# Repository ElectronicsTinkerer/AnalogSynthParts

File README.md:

# AnalogSynthParts
A collection of analog/midi related synth boards and schematics

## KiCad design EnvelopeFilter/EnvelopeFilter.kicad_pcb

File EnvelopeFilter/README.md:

# Envelope Filter
A simple ADSR-controlled VCF for use in panel-mount synthesizers.

## Interface
There are two inputs to the board:
- `IN` - Signal input (±15Vpp max) to be put into the envelope.
- `GATE` - Gate (active high) input for the ADSR envelope. Rising edge is treated as trigger.

 and one output:
 - `OUT` - Signal out of board after envelope has been applied.   

There is a bunch of 3-pin headers for connection to external potentiometers and switches to enable/disable various features like filter bypasses, manual frequency cutoff, and resonance.

### Power
This board is designed to be run off ±15V but with a few resistor swaps, it could be run off ±12V.   

## Schematic
The schematic for the ADSR section of the board is based off the *Soundtronics ADSR Type 1* design. It uses an `AS3310` ADSR control IC to generate the envelope control voltage. This is then fed through a resistor divider into the frequency control on an AS3320 VCF to adjust the cutoff frequency of each section of the filter, which is then sent to the output.  

## Board
The board is designed in a similar manner to the other ones in this repository, where it is supported by the potentiometers' leads. The pots are placed 1 inch apart for easy hole placement when designing the panel.

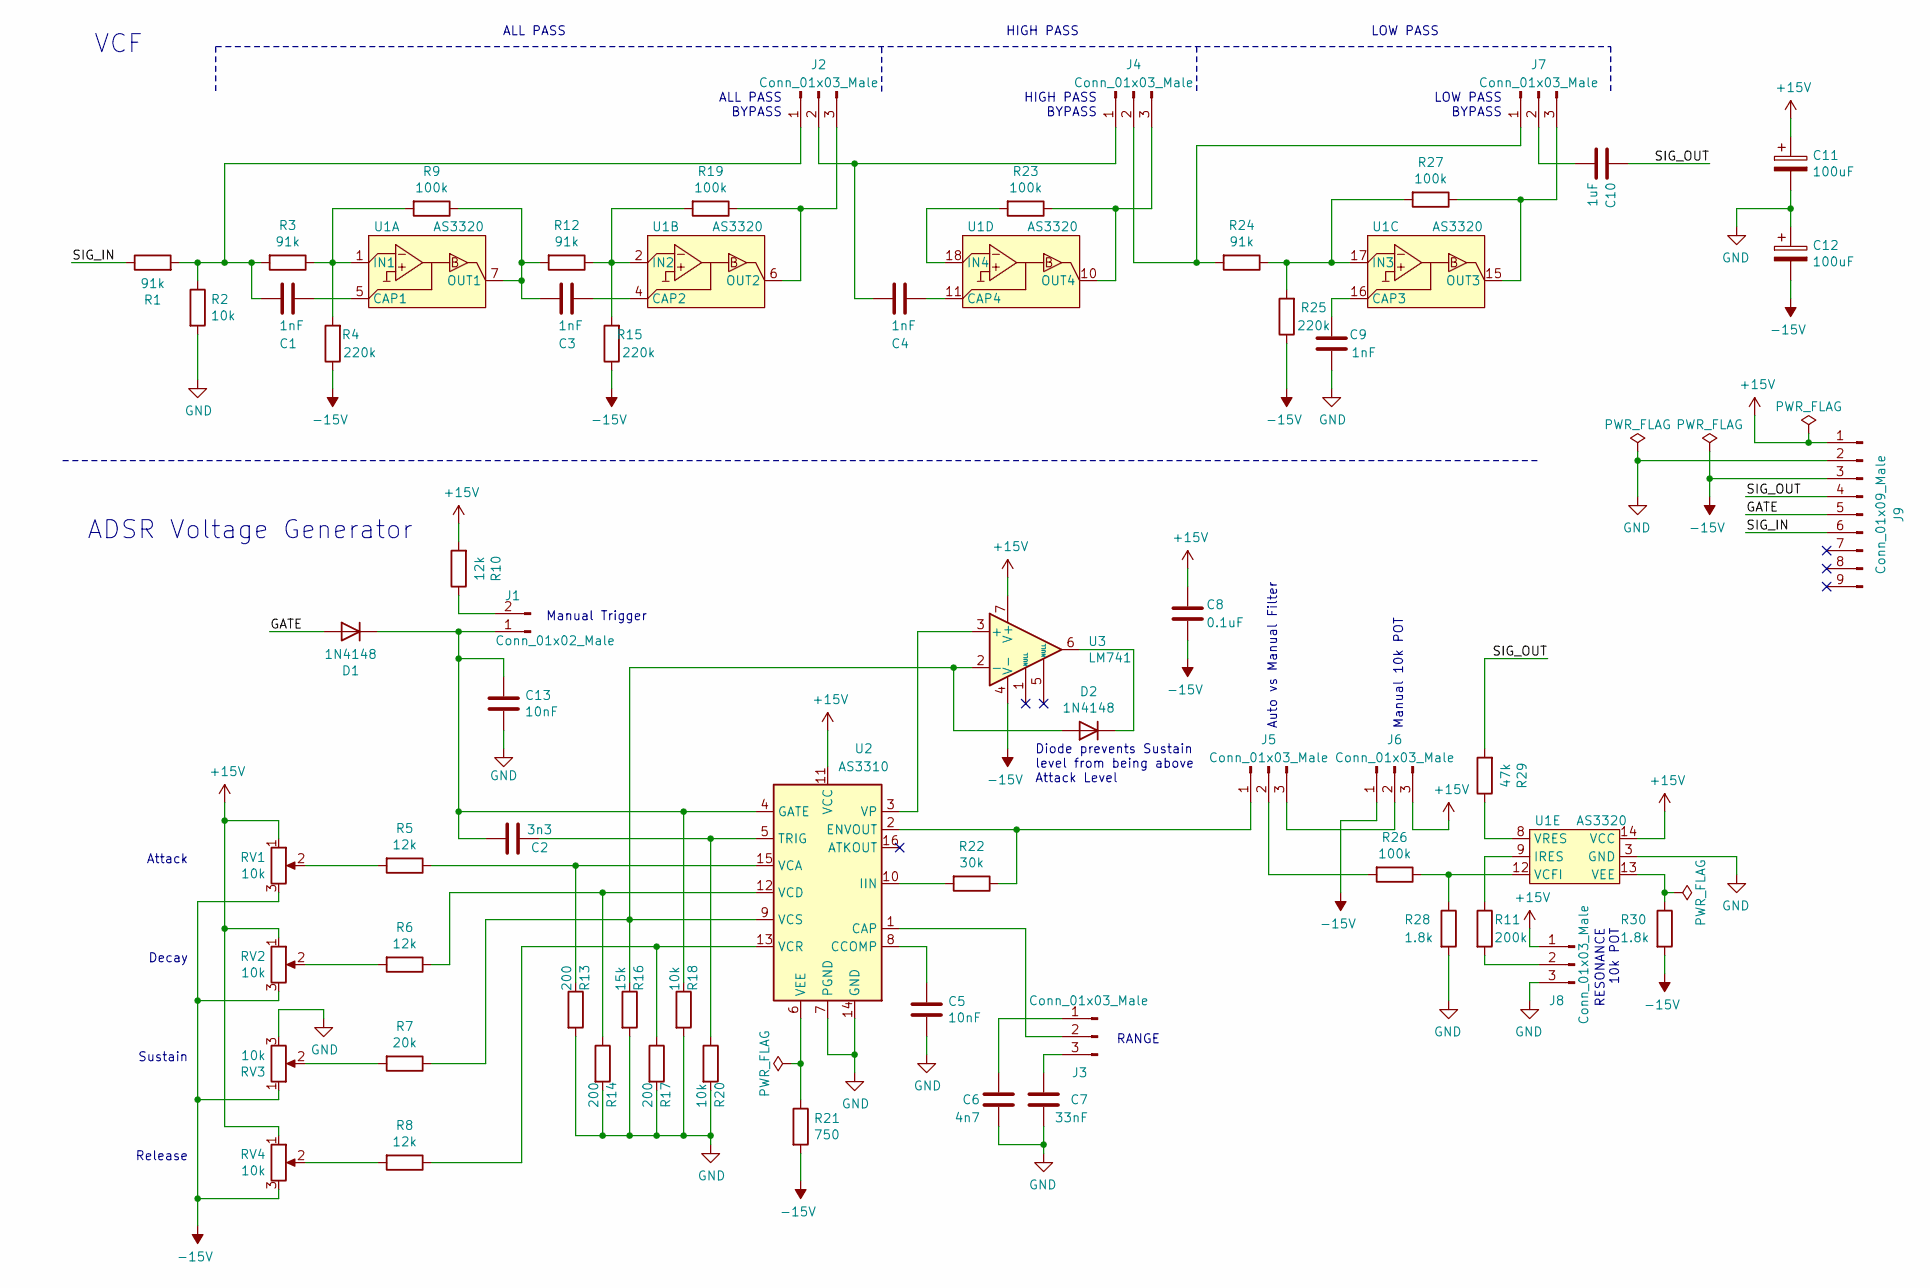
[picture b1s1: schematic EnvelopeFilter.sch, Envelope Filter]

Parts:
C1, C3, C4, C9: 1nF; C_Disc_D4.3mm_W1.9mm_P5.00mm
C2: 3n3; C_Disc_D4.3mm_W1.9mm_P5.00mm
C5: 10nF; C_Disc_D4.3mm_W1.9mm_P5.00mm
C6: 4n7; C_Disc_D4.3mm_W1.9mm_P5.00mm
C7: 33nF; C_Disc_D4.3mm_W1.9mm_P5.00mm
C8: 0.1uF; C_Disc_D4.3mm_W1.9mm_P5.00mm
C10: 1uF; C_Disc_D4.3mm_W1.9mm_P5.00mm
C11, C12: 100uF; CP_Radial_D8.0mm_P3.50mm
C13: 10nF; R_Axial_DIN0204_L3.6mm_D1.6mm_P5.08mm_Horizontal
D1, D2: 1N4148; D_DO-35_SOD27_P7.62mm_Horizontal
J1: Conn_01x02_Male; PinHeader_1x02_P2.54mm_Vertical
J2, J3, J4, J5, J6, J7, J8: Conn_01x03_Male; PinHeader_1x03_P2.54mm_Vertical
J9: Conn_01x09_Male; PinHeader_1x09_P2.54mm_Vertical
R1, R3, R12, R24: 91k; R_Axial_DIN0204_L3.6mm_D1.6mm_P5.08mm_Horizontal
R2, R18, R20: 10k; R_Axial_DIN0204_L3.6mm_D1.6mm_P5.08mm_Horizontal
R4, R15, R25: 220k; R_Axial_DIN0204_L3.6mm_D1.6mm_P5.08mm_Horizontal
R5, R6, R8, R10: 12k; R_Axial_DIN0204_L3.6mm_D1.6mm_P5.08mm_Horizontal
R7: 20k; R_Axial_DIN0204_L3.6mm_D1.6mm_P5.08mm_Horizontal
R9, R19, R23, R26, R27: 100k; R_Axial_DIN0204_L3.6mm_D1.6mm_P5.08mm_Horizontal
R11: 200k; R_Axial_DIN0204_L3.6mm_D1.6mm_P5.08mm_Horizontal
R13, R14, R17: 200; R_Axial_DIN0204_L3.6mm_D1.6mm_P5.08mm_Horizontal
R16: 15k; R_Axial_DIN0204_L3.6mm_D1.6mm_P5.08mm_Horizontal
R21: 750; R_Axial_DIN0414_L11.9mm_D4.5mm_P5.08mm_Vertical
R22: 30k; R_Axial_DIN0204_L3.6mm_D1.6mm_P5.08mm_Horizontal
R28, R30: 1.8k; R_Axial_DIN0204_L3.6mm_D1.6mm_P5.08mm_Horizontal
R29: 47k; R_Axial_DIN0204_L3.6mm_D1.6mm_P5.08mm_Horizontal
RV1, RV2, RV3, RV4: 10k; Potentiometer_Piher_PC-16_Single_Horizontal
U1: AS3320; DIP-18_W7.62mm
U2: AS3310; DIP-16_W7.62mm_Socket_LongPads
U3: LM741; DIP-8_W7.62mm_Socket_LongPads

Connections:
+15V: C8.2, C11.1, J6.3, J8.1, J9.1, R10.2, RV1.1, RV2.1, RV4.1, U1.14 (VCC), U2.11 (VCC), U3.7 (V+)
-15V: C8.1, C12.2, J6.1, J9.3, R4.1, R15.1, R21.2, R25.1, R30.2, RV1.3, RV2.3, RV3.1, RV4.3, U3.4 (V-)
/GATE: D1.2 (A), J9.5
/SIG_IN: J9.6, R1.1
/SIG_OUT: C10.2, J9.4, R29.2
GND: C5.1, C6.1, C7.1, C9.1, C11.2, C12.1, C13.1, J8.3, J9.2, R2.2, R13.2, R14.2, R16.2, R17.2, R18.2, R20.2, R28.2, RV3.3, U1.3 (GND), U2.7 (PGND), U2.14 (GND)
unnamed: C1.1, J2.1, R1.2, R2.1, R3.2
unnamed: C1.2, U1.5 (CAP1)
unnamed: C2.1, R20.1, U2.5 (TRIG)
unnamed: C3.1, R9.1, R12.2, U1.7 (OUT1)
unnamed: C3.2, U1.4 (CAP2)
unnamed: C4.1, J2.2, J4.1
unnamed: C4.2, U1.11 (CAP4)
unnamed: C5.2, U2.8 (CCOMP)
unnamed: C6.2, J3.1
unnamed: C7.2, J3.3
unnamed: C9.2, U1.16 (CAP3)
unnamed: C10.1, J7.2
unnamed: C2.2, C13.2, D1.1 (K), J1.1, R18.1, U2.4 (GATE)
unnamed: D2.1 (K), U3.6
unnamed: D2.2 (A), R7.1, R16.1, U2.9 (VCS), U3.2 (-)
unnamed: J1.2, R10.1
unnamed: J2.3, R19.1, U1.6 (OUT2)
unnamed: J3.2, U2.1 (CAP)
unnamed: J4.2, J7.1, R24.2
unnamed: J4.3, R23.1, U1.10 (OUT4)
unnamed: J5.1, R22.1, U2.2 (ENVOUT)
unnamed: J5.2, R26.2
unnamed: J5.3, J6.2
unnamed: J7.3, R27.1, U1.15 (OUT3)
unnamed: J8.2, R11.2
unnamed: R3.1, R4.2, R9.2, U1.1 (IN1)
unnamed: R5.2, RV1.2
unnamed: R6.2, RV2.2
unnamed: R7.2, RV3.2
unnamed: R8.2, RV4.2
unnamed: R11.1, U1.9 (IRES)
unnamed: R12.1, R15.2, R19.2, U1.2 (IN2)
unnamed: R5.1, R13.1, U2.15 (VCA)
unnamed: R6.1, R14.1, U2.12 (VCD)
unnamed: R8.1, R17.1, U2.13 (VCR)
unnamed: R21.1, U2.6 (VEE)
unnamed: R22.2, U2.10 (IIN)
unnamed: R23.2, U1.18 (IN4)
unnamed: R24.1, R25.2, R27.2, U1.17 (IN3)
unnamed: R26.1, R28.1, U1.12 (VCFI)
unnamed: R29.1, U1.8 (VRES)
unnamed: R30.1, U1.13 (VEE)
unnamed: U2.3 (VP), U3.3 (+)

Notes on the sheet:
RANGE
Diode prevents Sustain level from being above Attack Level
ADSR Voltage Generator
VCF
Manual Trigger
Attack
Decay
Sustain
Release
ALL PASS
HIGH PASS
LOW PASS
ALL PASS BYPASS
HIGH PASS BYPASS
LOW PASS BYPASS
Auto vs Manual Filter
Manual 10k POT
RESONANCE 10k POT

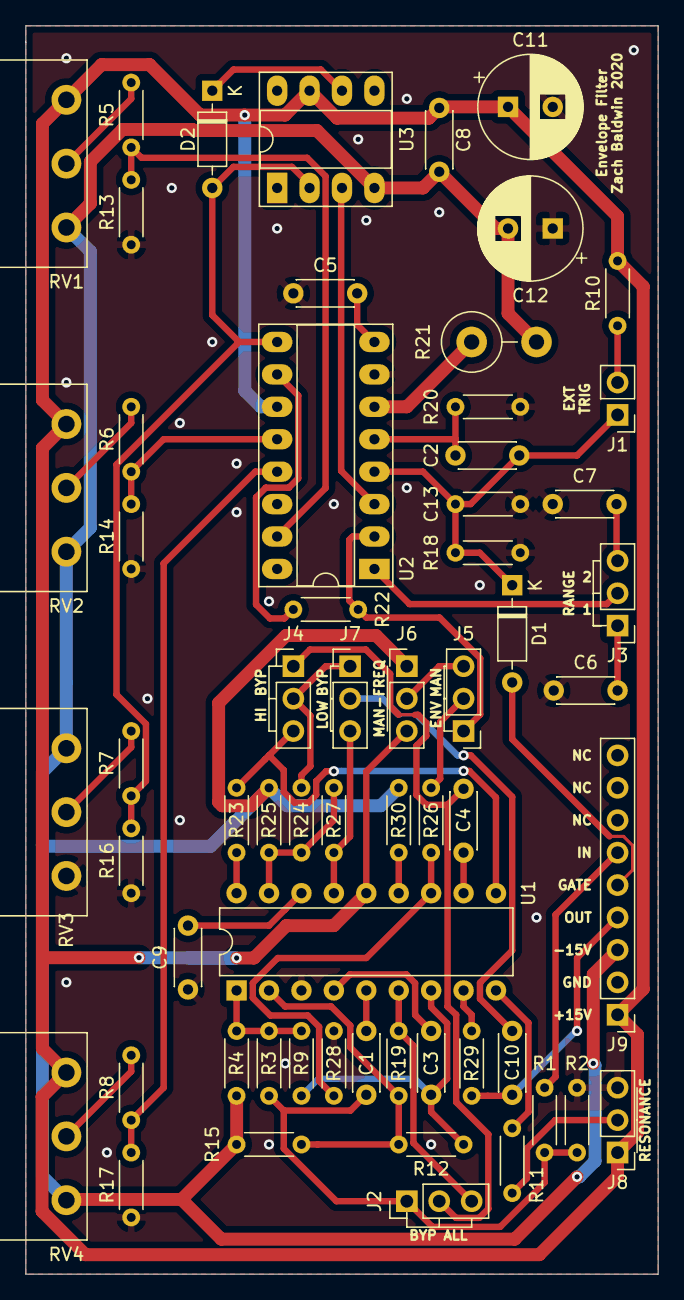
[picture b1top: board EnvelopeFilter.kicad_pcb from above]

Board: 2 copper layers, 49.5 x 97.8 mm, 61 parts (0 on the bottom side), 49 nets.

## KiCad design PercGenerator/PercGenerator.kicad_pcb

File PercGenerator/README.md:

# Percussion Synthesizer
A single op-amp "percussion synthesizer" redrawn from Forrest Mims III's *Getting Started in Electronics*

## Picture

## Interface
There are four potentiometers on the board. The leftmost three are for resonance cutoff (CCW is for cutoff, CW for resonance) and the rightmost potentiometer is gain out.   
This board uses the same connector pin out as the 555 Synth Module and each of the pins is marked on the board. Since not all of the pins were needed, four of them are marked "NC" and are unconnected. The remaining signals are:
- `T` - Triggers sound on both rising and falling edge
- `OUT` - Output waveform, this is connected via a potentiometer and a capacitor internally.

### Power
I run this board off ±15V, however, Mims uses ±9V in his book, so anywhere in that range should be fine. (While testing this circuit before I created the PCBs, I just used a +10v supply fed into a L7805 to create ±5V and that worked just fine).

## Schematic
The schematic is a simple feedback oscillator with three 1M potentiometers to adjust the resonance. The schematic is the same as one in Mims' book, except for the addition of a transistor in parallel with the trigger switch.

## Board
The board really could have been laid out however one wanted, but I chose to put the control potentiometers 1" apart on one side of the board. There are two "mounting holes" that are grounded in case anyone wants to mount the board more securely than just being held on via the potentiometers.

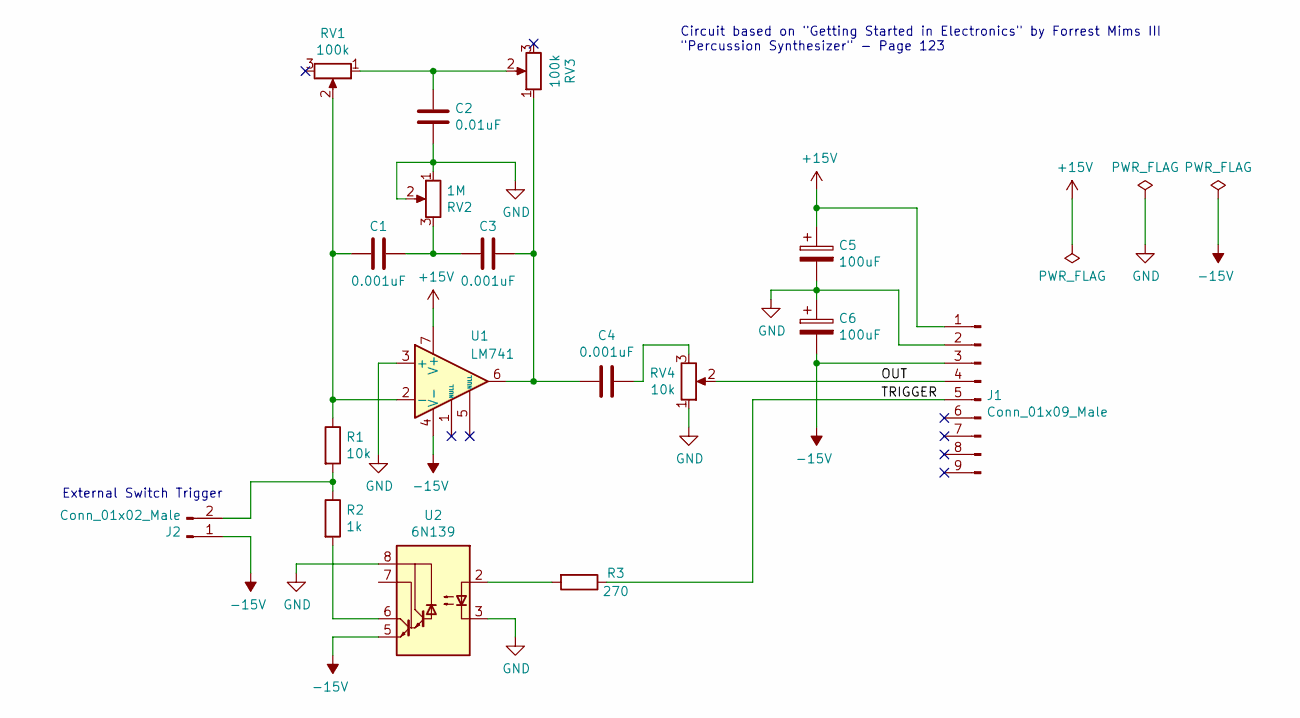
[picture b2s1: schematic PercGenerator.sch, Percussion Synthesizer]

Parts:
C1, C3, C4: 0.001uF; C_Disc_D4.3mm_W1.9mm_P5.00mm
C2: 0.01uF; C_Disc_D4.3mm_W1.9mm_P5.00mm
C5, C6: 100uF; CP_Radial_D8.0mm_P3.50mm
J1: Conn_01x09_Male; PinHeader_1x09_P2.54mm_Vertical
J2: Conn_01x02_Male; PinHeader_1x02_P2.54mm_Vertical
R1: 10k; R_Axial_DIN0204_L3.6mm_D1.6mm_P5.08mm_Horizontal
R2: 1k; R_Axial_DIN0204_L3.6mm_D1.6mm_P5.08mm_Horizontal
R3: 270; R_Axial_DIN0204_L3.6mm_D1.6mm_P5.08mm_Horizontal
RV1, RV3: 100k; Potentiometer_Piher_PC-16_Single_Horizontal
RV2: 1M; Potentiometer_Piher_PC-16_Single_Horizontal
RV4: 10k; Potentiometer_Piher_PC-16_Single_Horizontal
U1: LM741; DIP-8_W7.62mm_LongPads
U2: 6N139; DIP-8_W7.62mm_LongPads

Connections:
+15V: C5.1, J1.1, U1.7 (V+)
-15V: C6.2, J1.3, J2.1, U1.4 (V-), U2.5 (GND)
/OUT: J1.4, RV4.2
/TRIGGER: J1.5, R3.1
GND: C2.2, C5.2, C6.1, J1.2, RV2.1, RV2.2, RV4.1, U1.3 (+), U2.3 (C2), U2.8 (VCC)
unnamed: C1.1, C3.2, RV2.3
unnamed: C1.2, R1.1, RV1.2, U1.2 (-)
unnamed: C2.1, RV1.1, RV3.2
unnamed: C3.1, C4.2, RV3.1, U1.6
unnamed: C4.1, RV4.3
unnamed: J2.2, R1.2, R2.1
unnamed: R2.2, U2.6 (VO2)
unnamed: R3.2, U2.2 (C1)

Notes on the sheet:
Circuit based on "Getting Started in Electronics" by Forrest Mims III "Percussion Synthesizer" - Page 123
External Switch Trigger

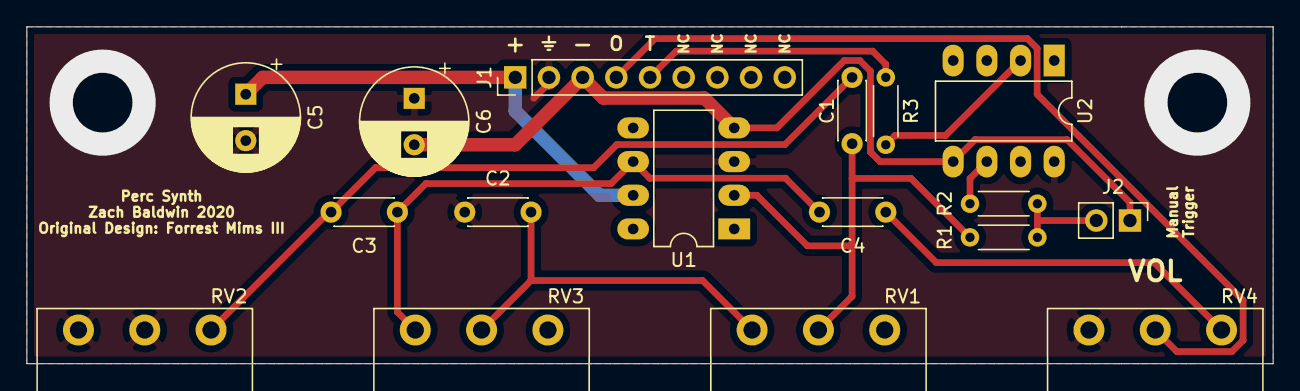
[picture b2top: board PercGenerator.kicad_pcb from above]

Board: 2 copper layers, 94.0 x 25.4 mm, 17 parts (0 on the bottom side), 13 nets.

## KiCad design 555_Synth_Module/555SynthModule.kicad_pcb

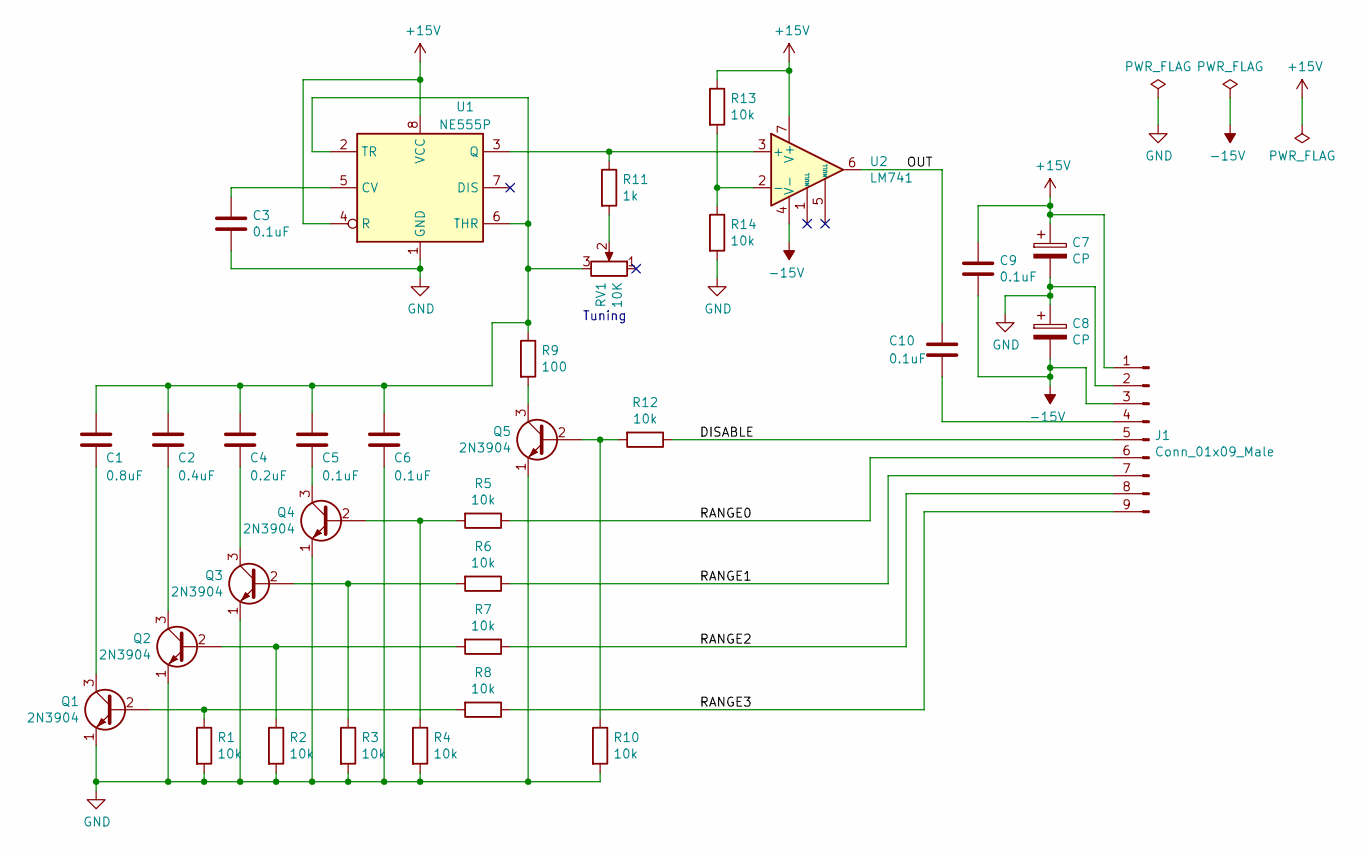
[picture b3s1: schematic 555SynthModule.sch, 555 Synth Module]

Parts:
C1: 0.8uF; C_Disc_D4.3mm_W1.9mm_P5.00mm
C2: 0.4uF; C_Disc_D4.3mm_W1.9mm_P5.00mm
C3, C5, C6, C9, C10: 0.1uF; C_Disc_D4.3mm_W1.9mm_P5.00mm
C4: 0.2uF; C_Disc_D4.3mm_W1.9mm_P5.00mm
C7, C8: CP; CP_Radial_D8.0mm_P3.50mm
J1: Conn_01x09_Male; PinHeader_1x09_P2.54mm_Vertical
Q1, Q2, Q3, Q4, Q5: 2N3904; TO-92_Inline
R1, R2, R3, R4, R5, R6, R7, R8, R10, R12, R13, R14: 10k; R_Axial_DIN0204_L3.6mm_D1.6mm_P5.08mm_Horizontal
R9: 100; R_Axial_DIN0204_L3.6mm_D1.6mm_P5.08mm_Horizontal
R11: 1k; R_Axial_DIN0204_L3.6mm_D1.6mm_P5.08mm_Horizontal
RV1: 10K; Potentiometer_Piher_PC-16_Single_Horizontal
U1: NE555P; DIP-8_W7.62mm
U2: LM741; DIP-8_W7.62mm

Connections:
+15V: C7.1, C9.1, J1.1, R13.1, U1.4 (R), U1.8 (VCC), U2.7 (V+)
-15V: C8.2, C9.2, J1.3, U2.4 (V-)
/DISABLE: J1.5, R12.1
/OUT: C10.1, U2.6
/RANGE0: J1.6, R5.1
/RANGE1: J1.7, R6.1
/RANGE2: J1.8, R7.1
/RANGE3: J1.9, R8.1
GND: C3.2, C6.2, C7.2, C8.1, J1.2, Q1.1 (E), Q2.1 (E), Q3.1 (E), Q4.1 (E), Q5.1 (E), R1.2, R2.2, R3.2, R4.2, R10.2, R14.2, U1.1 (GND)
unnamed: C1.1, C2.1, C4.1, C5.1, C6.1, R9.1, RV1.3, U1.2 (TR), U1.6 (THR)
unnamed: C1.2, Q1.3 (C)
unnamed: C2.2, Q2.3 (C)
unnamed: C3.1, U1.5 (CV)
unnamed: C4.2, Q3.3 (C)
unnamed: C5.2, Q4.3 (C)
unnamed: C10.2, J1.4
unnamed: Q1.2 (B), R1.1, R8.2
unnamed: Q2.2 (B), R2.1, R7.2
unnamed: Q3.2 (B), R3.1, R6.2
unnamed: Q4.2 (B), R4.1, R5.2
unnamed: Q5.2 (B), R10.1, R12.2
unnamed: Q5.3 (C), R9.2
unnamed: R11.1, U1.3 (Q), U2.3 (+)
unnamed: R11.2, RV1.2
unnamed: R13.2, R14.1, U2.2 (-)

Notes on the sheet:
Tuning

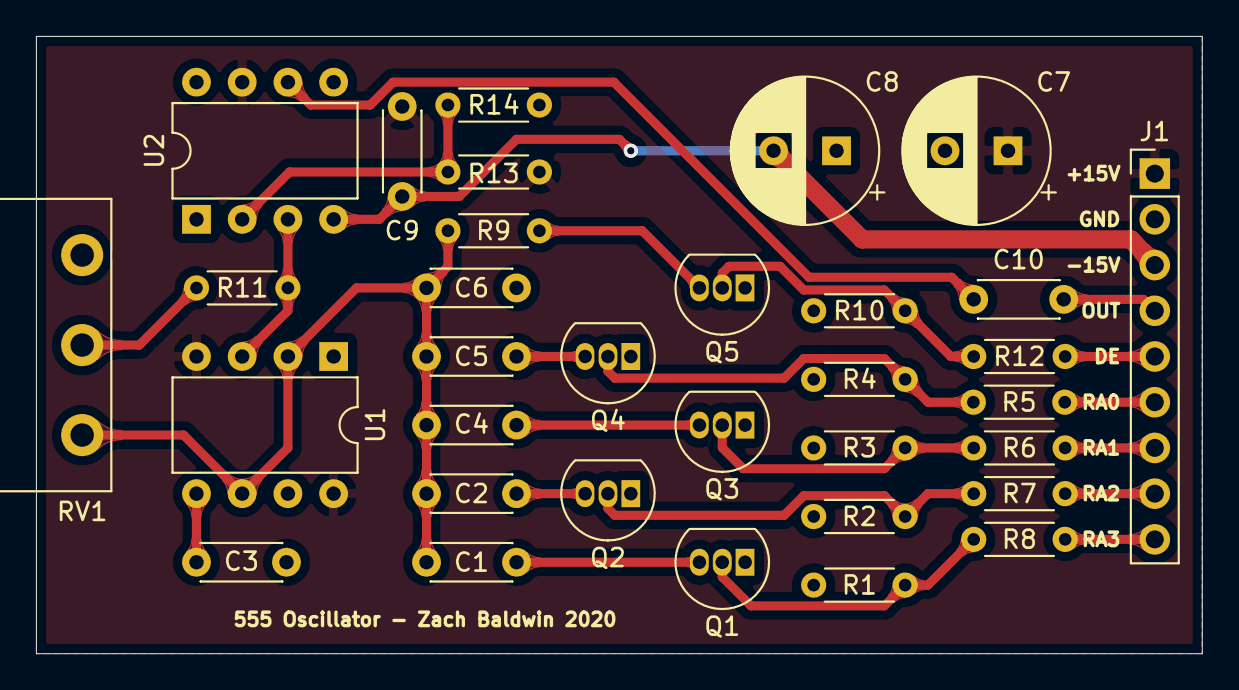
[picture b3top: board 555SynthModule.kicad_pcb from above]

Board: 2 copper layers, 64.8 x 34.3 mm, 33 parts (0 on the bottom side), 25 nets.

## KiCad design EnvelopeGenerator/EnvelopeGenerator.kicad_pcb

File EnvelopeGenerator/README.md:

# Envelope Generator
A simple ADSR-controlled VCA for use in panel-mount synthesizers.

## Interface
There are two inputs to the board:
- `IN` - Signal input (±15Vpp max) to be put into the envelope.
- `GATE` - Gate (active high) input for the ADSR envelope. Rising edge is treated as trigger.

 and one output:
 - `OUT` - Signal out of board after envelope has been applied.

### Power
Unlike the other modules in this repository, this board needs a ±15V supply since one of the ICs has its own set of ±12V regulators. (Although, I suppose you could just bypass the regulators if you wanted to run it off ±12V).   

## Schematic
The schematic for the ADSR section of the board is based off the *Soundtronics ADSR Type 1* design. It uses an `AS3310` ADSR control IC to generate the envelope control voltage. This is then fed through a resistor divider into the gain control on an AS3360 VCA to modulate the amplitude of the input signal, which is then sent to the output.  
There is a on-board ±12V power supply for the AS3360.

## Board
The board is designed in a similar manner to the other ones in this repository, where it is supported by the potentiometers' leads. The pots are placed 1 inch apart for easy hole placement when designing the panel. There are two external switches. The first, connected to `J2` is for setting the range of slopes for the envelope (This one is needed or solder a jumper on the appropriate contacts if not wired.) The second switch (`J1`) is for a secondary gate/trigger input. This one is optional.

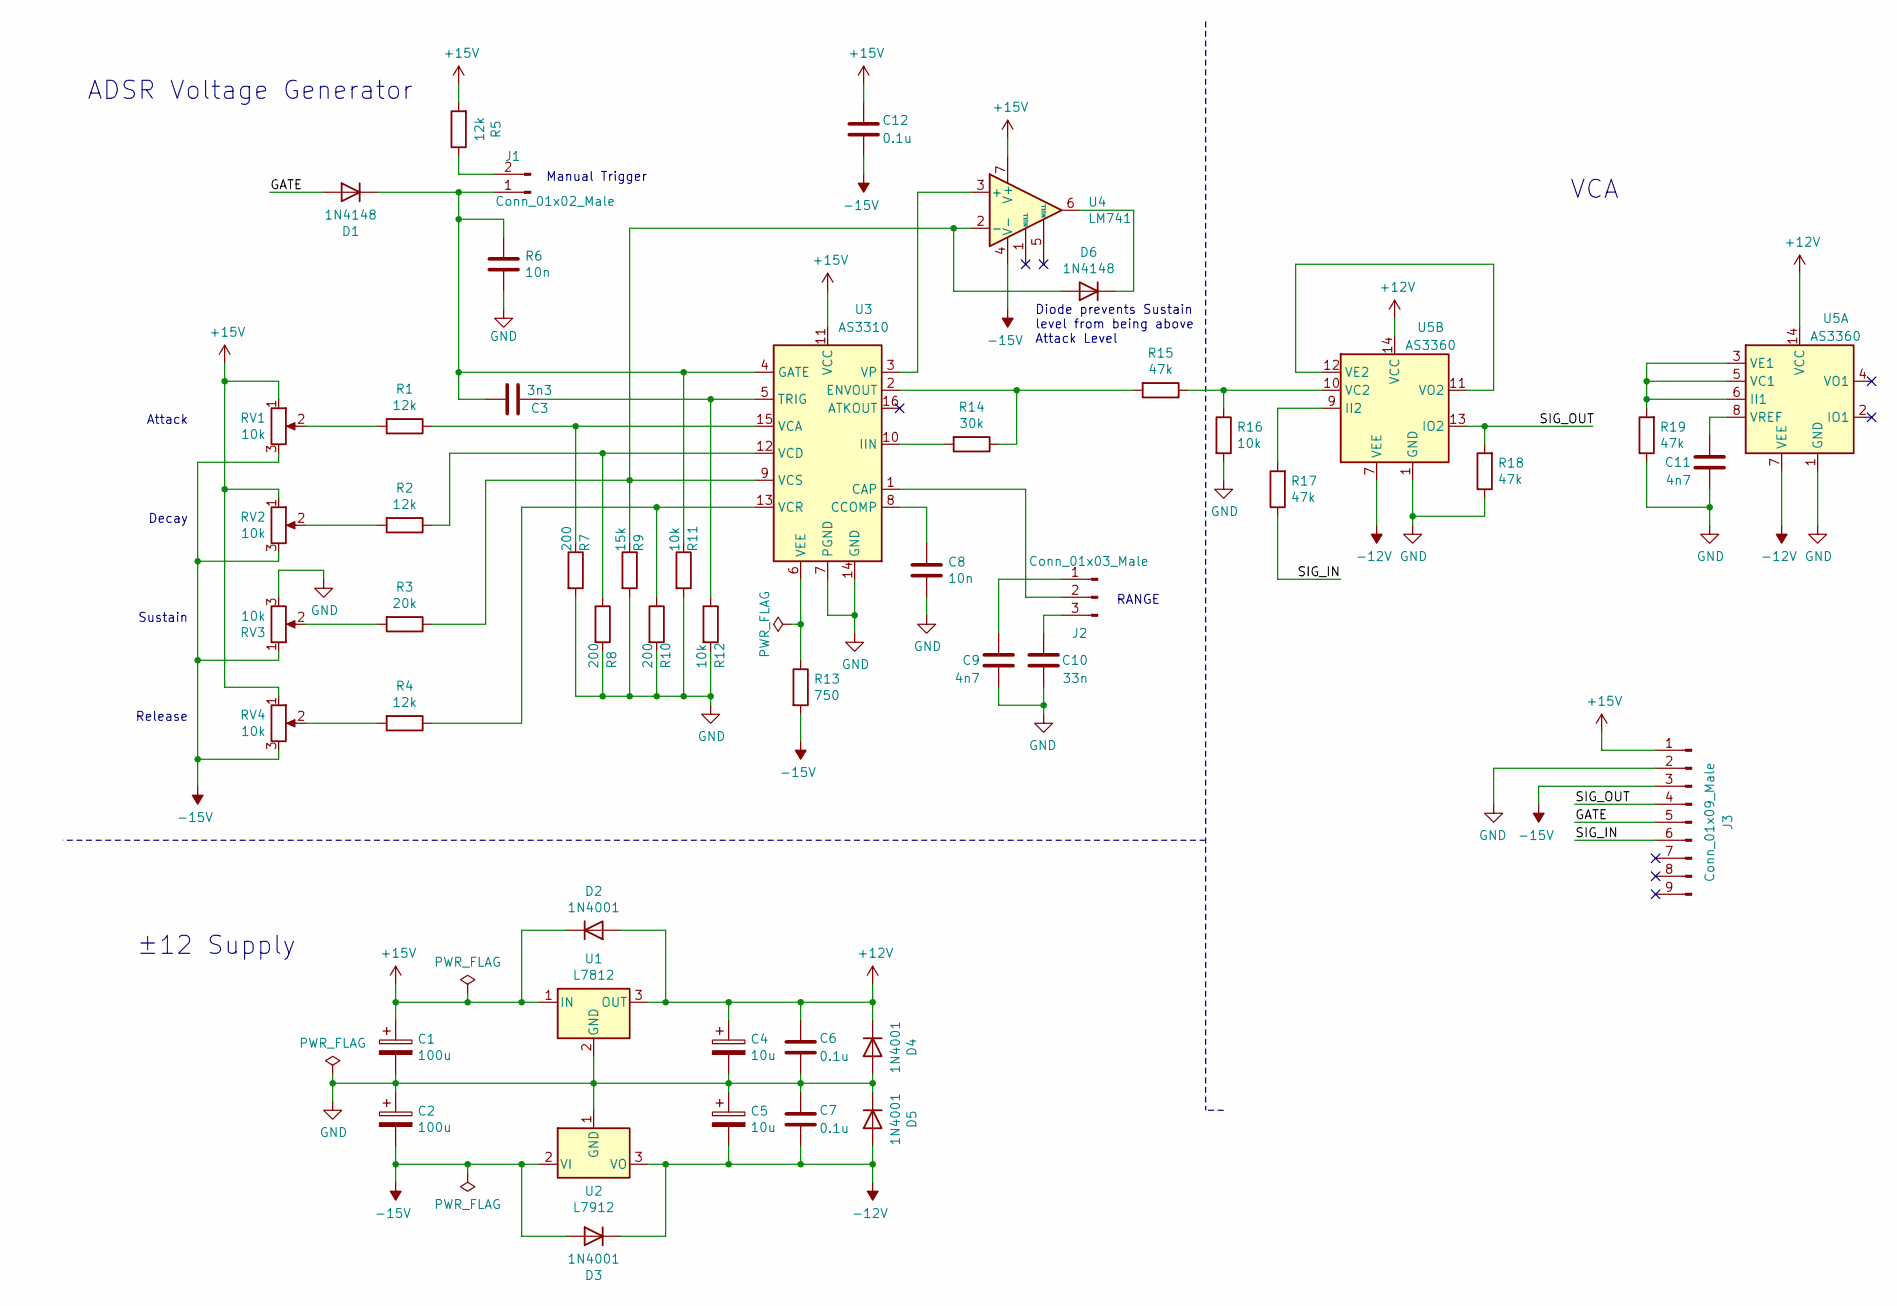
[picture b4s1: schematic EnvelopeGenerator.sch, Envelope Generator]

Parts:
C1, C2: 100u; CP_Radial_D8.0mm_P3.50mm
C3: 3n3; C_Disc_D4.3mm_W1.9mm_P5.00mm
C4, C5: 10u; CP_Radial_D8.0mm_P3.50mm
C6, C7, C12: 0.1u; C_Disc_D4.3mm_W1.9mm_P5.00mm
C8: 10n; C_Disc_D4.3mm_W1.9mm_P5.00mm
C9, C11: 4n7; C_Disc_D4.3mm_W1.9mm_P5.00mm
C10: 33n; C_Disc_D4.3mm_W1.9mm_P5.00mm
D1, D6: 1N4148; D_DO-35_SOD27_P7.62mm_Horizontal
D2, D3, D4, D5: 1N4001; D_DO-35_SOD27_P7.62mm_Horizontal
J1: Conn_01x02_Male; PinHeader_1x02_P2.54mm_Vertical
J2: Conn_01x03_Male; PinHeader_1x03_P2.54mm_Vertical
J3: Conn_01x09_Male; PinHeader_1x09_P2.54mm_Vertical
R1, R2, R4, R5: 12k; R_Axial_DIN0204_L3.6mm_D1.6mm_P5.08mm_Horizontal
R3: 20k; R_Axial_DIN0204_L3.6mm_D1.6mm_P5.08mm_Horizontal
R6: 10n; R_Axial_DIN0204_L3.6mm_D1.6mm_P5.08mm_Horizontal
R7, R8, R10: 200; R_Axial_DIN0204_L3.6mm_D1.6mm_P5.08mm_Horizontal
R9: 15k; R_Axial_DIN0204_L3.6mm_D1.6mm_P5.08mm_Horizontal
R11, R12, R16: 10k; R_Axial_DIN0204_L3.6mm_D1.6mm_P5.08mm_Horizontal
R13: 750; R_Axial_DIN0414_L11.9mm_D4.5mm_P5.08mm_Vertical
R14: 30k; R_Axial_DIN0204_L3.6mm_D1.6mm_P5.08mm_Horizontal
R15, R17, R18, R19: 47k; R_Axial_DIN0204_L3.6mm_D1.6mm_P5.08mm_Horizontal
RV1, RV2, RV3, RV4: 10k; Potentiometer_Piher_PC-16_Single_Horizontal
U1: L7812; TO-220-3_Vertical
U2: L7912; TO-220-3_Vertical
U3: AS3310; DIP-16_W7.62mm_Socket_LongPads
U4: LM741; DIP-8_W7.62mm_Socket_LongPads
U5: AS3360; DIP-14_W7.62mm_Socket_LongPads

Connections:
+12V: C4.1, C6.2, D2.2 (A), D4.1 (K), U1.3 (OUT), U5.14 (VCC)
+15V: C1.1, C12.2, D2.1 (K), J3.1, R5.2, RV1.1, RV2.1, RV4.1, U1.1 (IN), U3.11 (VCC), U4.7 (V+)
-12V: C5.2, C7.1, D3.1 (K), D5.2 (A), U2.3 (VO), U5.7 (VEE)
-15V: C2.2, C12.1, D3.2 (A), J3.3, R13.2, RV1.3, RV2.3, RV3.1, RV4.3, U2.2 (VI), U4.4 (V-)
/GATE: D1.2 (A), J3.5
/SIG_IN: J3.6, R17.1
/SIG_OUT: J3.4, R18.2, U5.13 (IO2)
GND: C1.2, C2.1, C4.2, C5.1, C6.1, C7.2, C8.1, C9.1, C10.1, C11.1, D4.2 (A), D5.1 (K), J3.2, R6.1, R7.2, R8.2, R9.2, R10.2, R11.2, R12.2, R16.2, R18.1, R19.1, RV3.3, U1.2 (GND), U2.1 (GND), U3.7 (PGND), U3.14 (GND), U5.1 (GND); also elsewhere on the board
unnamed: C3.1, R12.1, U3.5 (TRIG)
unnamed: C8.2, U3.8 (CCOMP)
unnamed: C9.2, J2.1
unnamed: C10.2, J2.3
unnamed: C11.2, U5.8 (VREF)
unnamed 13: C3.2, D1.1 (K), J1.1, R6.2, R11.1, U3.4 (GATE); also elsewhere on the board
unnamed: D6.1 (K), U4.6
unnamed: D6.2 (A), R3.1, R9.1, U3.9 (VCS), U4.2 (-)
unnamed: J1.2, R5.1
unnamed: J2.2, U3.1 (CAP)
unnamed: R1.1, R7.1, U3.15 (VCA)
unnamed: R1.2, RV1.2
unnamed: R2.1, R8.1, U3.12 (VCD)
unnamed: R2.2, RV2.2
unnamed: R3.2, RV3.2
unnamed: R4.2, RV4.2
unnamed: R4.1, R10.1, U3.13 (VCR)
unnamed: R13.1, U3.6 (VEE)
unnamed: R14.1, R15.2, U3.2 (ENVOUT)
unnamed: R14.2, U3.10 (IIN)
unnamed: R15.1, R16.1, U5.10 (VC2)
unnamed: R17.2, U5.9 (II2)
unnamed: R19.2, U5.3 (VE1), U5.5 (VC1), U5.6 (II1)
unnamed: U3.3 (VP), U4.3 (+)
unnamed: U5.11 (VO2), U5.12 (VE2)

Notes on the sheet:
RANGE
Diode prevents Sustain level from being above Attack Level
ADSR Voltage Generator
VCA
±12 Supply
Manual Trigger
Attack
Decay
Sustain
Release

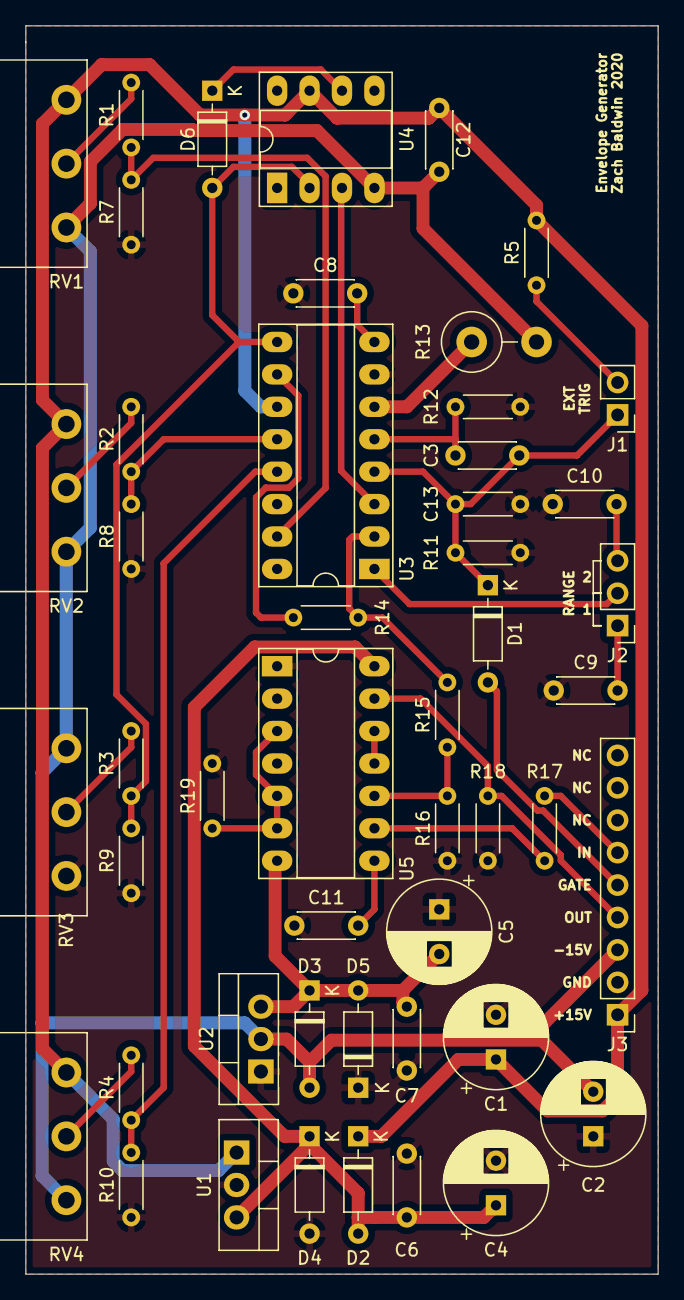
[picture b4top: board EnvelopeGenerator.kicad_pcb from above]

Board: 2 copper layers, 49.5 x 97.8 mm, 49 parts (0 on the bottom side), 33 nets.

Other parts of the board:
C13: 10n; R_Axial_DIN0204_L3.6mm_D1.6mm_P5.08mm_Horizontal

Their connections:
GND: C13.1; also elsewhere on the board
unnamed 13: C13.2; also elsewhere on the board

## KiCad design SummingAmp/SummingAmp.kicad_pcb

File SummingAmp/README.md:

# Multi-mode Op Amp Summer
A three-mode op-amp inverting summing amplifier.

## Interface
Aside from power, there is only one signal on the main connector:
 - `OUT` - Signal out of board after envelope has been applied.   

There are also two 3-pin headers for use in selecting they input component (resistive or capacitive) and the feedback component (resistive or resistive-capacitive). These allow the board to be configured as an inverting summing amplifier, an RC-integrator, and an RC-differentiator.

### Power
The only power requirements are those of the 741 op amp, so basically any plus/minus supply should work (up to ±15V). If you do not have a dual rail supply, this can be powered off a single rail by connecting the `-V` to the low side of your supply, `+V` to the high side, and using a resistor divider (10k-100k should work fine) to get a center voltage to be connected to `GND`.   

## Schematic
The schematic is basically just an inverting summing amplifier that has switches to adjust the various input and feedback components.

## Board
The board is designed in a similar manner to the other ones in this repository, where it is supported by the potentiometer's leads. There is a power connector (left), 20 signal inputs (bottom), and the two option connections on the (right) for the circuit's mode.

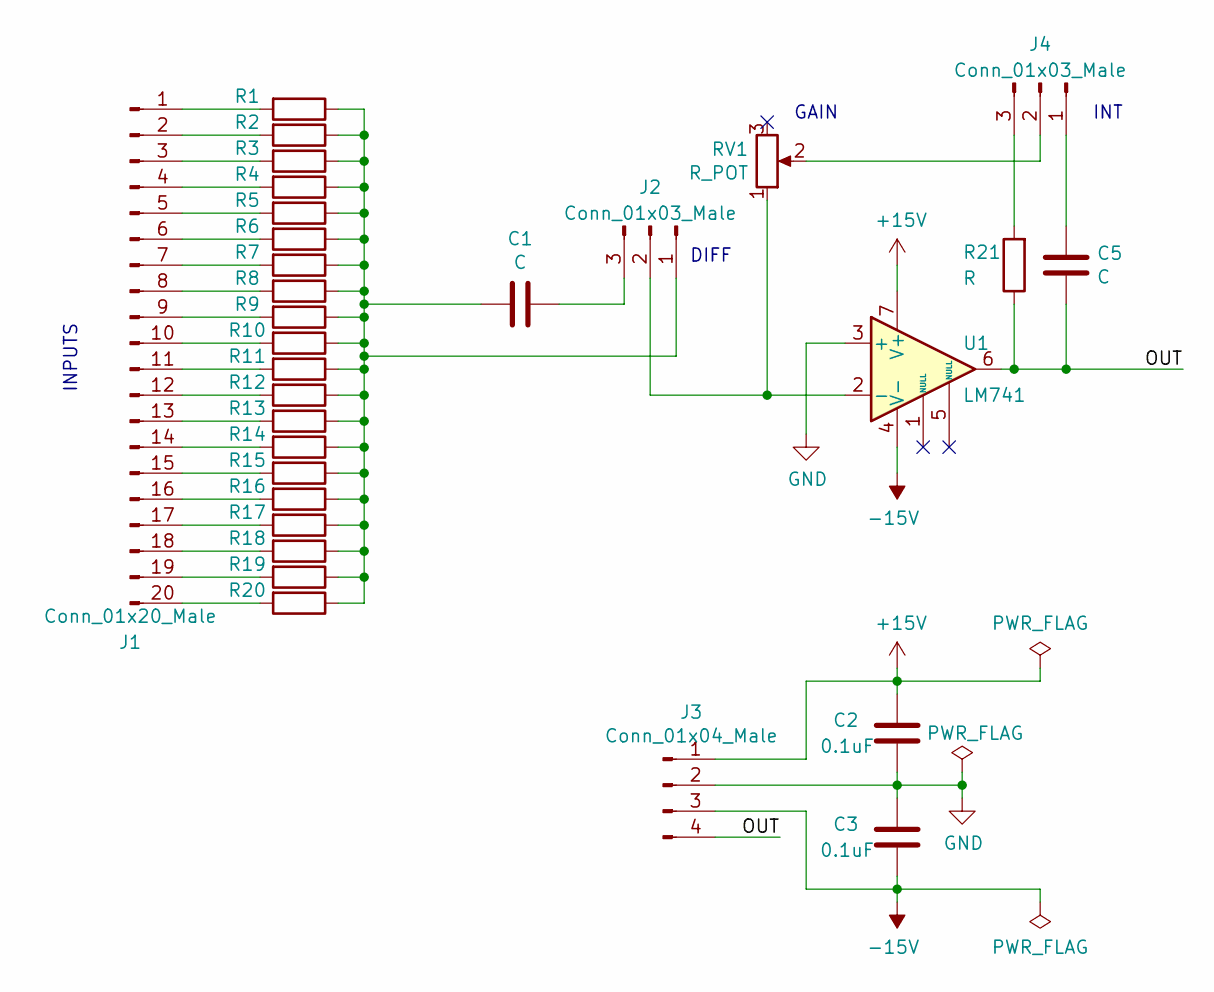
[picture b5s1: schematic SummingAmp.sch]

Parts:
C1, C5: C; C_Disc_D4.3mm_W1.9mm_P5.00mm
C2, C3: 0.1uF; C_Disc_D4.3mm_W1.9mm_P5.00mm
J1: Conn_01x20_Male; PinHeader_1x20_P2.54mm_Vertical
J2, J4: Conn_01x03_Male; PinHeader_1x03_P2.54mm_Vertical
J3: Conn_01x04_Male; PinHeader_1x04_P2.54mm_Vertical
R1, R2, R3, R4, R5, R6, R7, R8, R9, R10, R11, R12, R13, R14, R15, R16, R17, R18, R19, R20, R21: R; R_Axial_DIN0204_L3.6mm_D1.6mm_P5.08mm_Horizontal
RV1: R_POT; Potentiometer_Piher_PC-16_Single_Horizontal
U1: LM741; DIP-8_W7.62mm_LongPads

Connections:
+15V: C2.1, J3.1, U1.7 (V+)
-15V: C3.2, J3.3, U1.4 (V-)
/OUT: C5.1, J3.4, R21.1, U1.6
GND: C2.2, C3.1, J3.2, U1.3 (+)
unnamed: C1.1, J2.1, R1.1, R2.1, R3.1, R4.1, R5.1, R6.1, R7.1, R8.1, R9.1, R10.1, R11.1, R12.1, R13.1, R14.1, R15.1, R16.1, R17.1, R18.1, R19.1, R20.1
unnamed: C1.2, J2.3
unnamed: C5.2, J4.1
unnamed: J1.1, R1.2
unnamed: J1.2, R2.2
unnamed: J1.3, R3.2
unnamed: J1.4, R4.2
unnamed: J1.5, R5.2
unnamed: J1.6, R6.2
unnamed: J1.7, R7.2
unnamed: J1.8, R8.2
unnamed: J1.9, R9.2
unnamed: J1.10, R10.2
unnamed: J1.11, R11.2
unnamed: J1.12, R12.2
unnamed: J1.13, R13.2
unnamed: J1.14, R14.2
unnamed: J1.15, R15.2
unnamed: J1.16, R16.2
unnamed: J1.17, R17.2
unnamed: J1.18, R18.2
unnamed: J1.19, R19.2
unnamed: J1.20, R20.2
unnamed: J2.2, RV1.1, U1.2 (-)
unnamed: J4.2, RV1.2
unnamed: J4.3, R21.2

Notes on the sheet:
INPUTS
DIFF
GAIN
INT

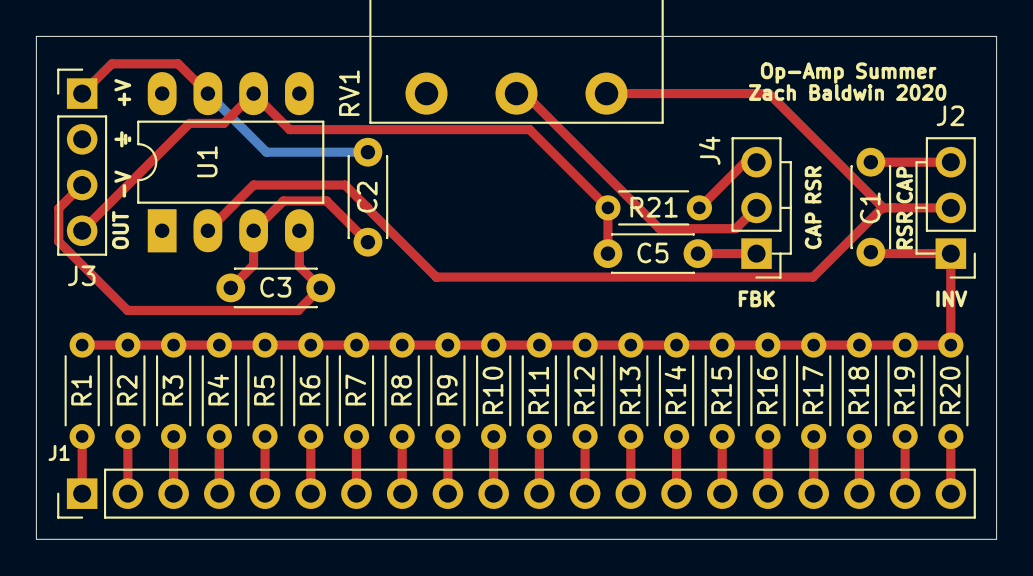
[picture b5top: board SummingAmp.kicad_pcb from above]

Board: 2 copper layers, 53.3 x 27.9 mm, 31 parts (0 on the bottom side), 30 nets.
